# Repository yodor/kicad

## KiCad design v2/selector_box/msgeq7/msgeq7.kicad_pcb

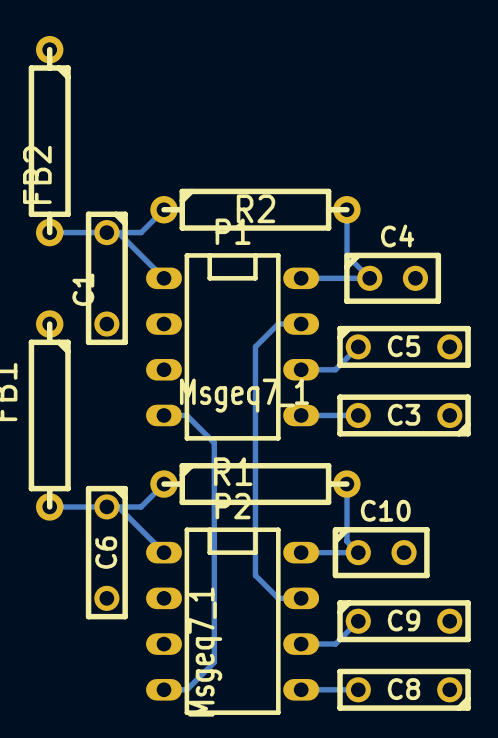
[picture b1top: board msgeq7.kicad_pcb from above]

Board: 2 copper layers, 14 parts (0 on the bottom side), 12 nets.

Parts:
C1, C5, C6, C9: 100nF; C2
C3, C8: 1uF; C2
C4, C10: 33pF; C1
FB1, FB2: FILTER; R4
P1, P2: Msgeq7_1; DIP-8__300
R1, R2: 200K; R4

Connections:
/5V: FB1.1, FB2.1
/RST: P1.7, P2.7
/Strobe: P1.4, P2.4
GND: C1.2, C4.2, C5.2, C6.2, C9.2, C10.2, P1.2, P2.2
unnamed: C9.1, P2.6
unnamed: C10.1, P2.8, R1.2
unnamed: C8.2, P2.5
unnamed: C6.1, FB1.2, P2.1, R1.1
unnamed: C5.1, P1.6
unnamed: C3.2, P1.5
unnamed: C1.1, FB2.2, P1.1, R2.1
unnamed: C4.1, P1.8, R2.2

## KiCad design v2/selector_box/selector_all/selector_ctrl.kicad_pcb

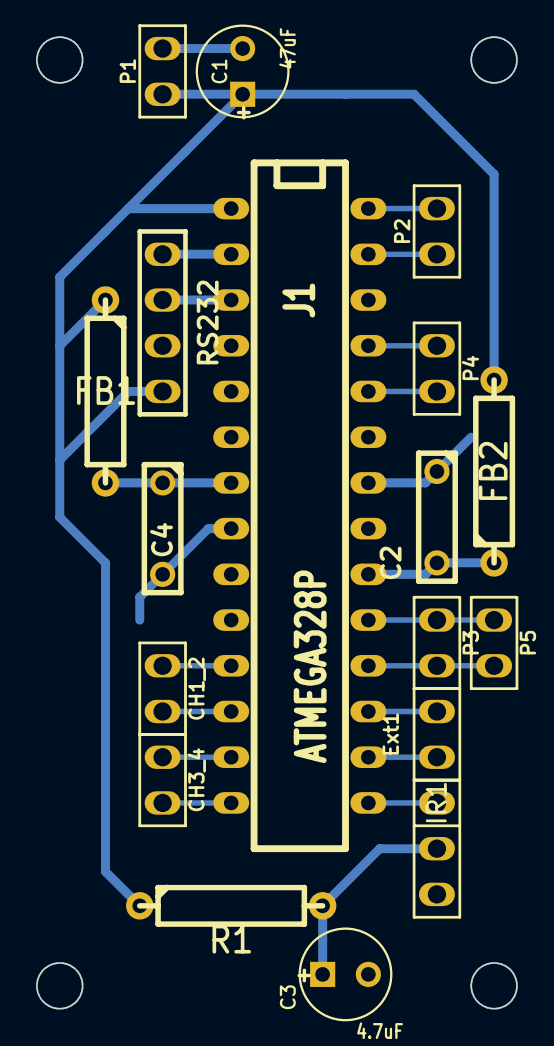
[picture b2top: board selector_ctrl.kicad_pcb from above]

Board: 2 copper layers, 26.7 x 54.0 mm, 18 parts (0 on the bottom side), 20 nets.

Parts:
C1: 47uF; C1V5
C2, C4: 100nF; C2
C3: 4.7uF; C1V5
CH1_2, CH3_4: CONN_2; PIN_ARRAY_2X1
Ext1: CONN_2; PIN_ARRAY_2X1
FB1, FB2: FILTER; R4
IR1: CONN_3; PIN_ARRAY_3X1
J1: ATMEGA328P; DIP-28__300
P1, P2, P3, P4, P5: CONN_2; PIN_ARRAY_2X1
R1: 100R; R4
RS232: CONN_4; PIN_ARRAY_4x1

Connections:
/5V: C1.1, FB1.1, FB2.2, J1.1, P1.1, R1.1, RS232.4
/CH1: CH1_2.1, J1.11
/CH2: CH1_2.2, J1.12
/CH3: CH3_4.1, J1.13
/CH4: CH3_4.2, J1.14
/EQ7_DATA_L: J1.25, P4.1
/EQ7_DATA_R: J1.24, P4.2
/EQ7_RST: J1.18, P3.2, P5.2
/EQ7_STROBE: J1.19, P3.1, P5.1
/EXT1: Ext1.1, J1.17
/EXT2: Ext1.2, J1.16
/IR: IR1.1, J1.15
/RX: J1.2, RS232.1
/SCL: J1.28, P2.2
/SDA: J1.27, P2.1
/TX: J1.3, RS232.2
GND: C1.2, C2.1, C3.2, C4.2, IR1.3, J1.8, J1.22, P1.2, RS232.3
unnamed: C2.2, FB2.1, J1.20
unnamed: C4.1, FB1.2, J1.7
unnamed: C3.1, IR1.2, R1.2

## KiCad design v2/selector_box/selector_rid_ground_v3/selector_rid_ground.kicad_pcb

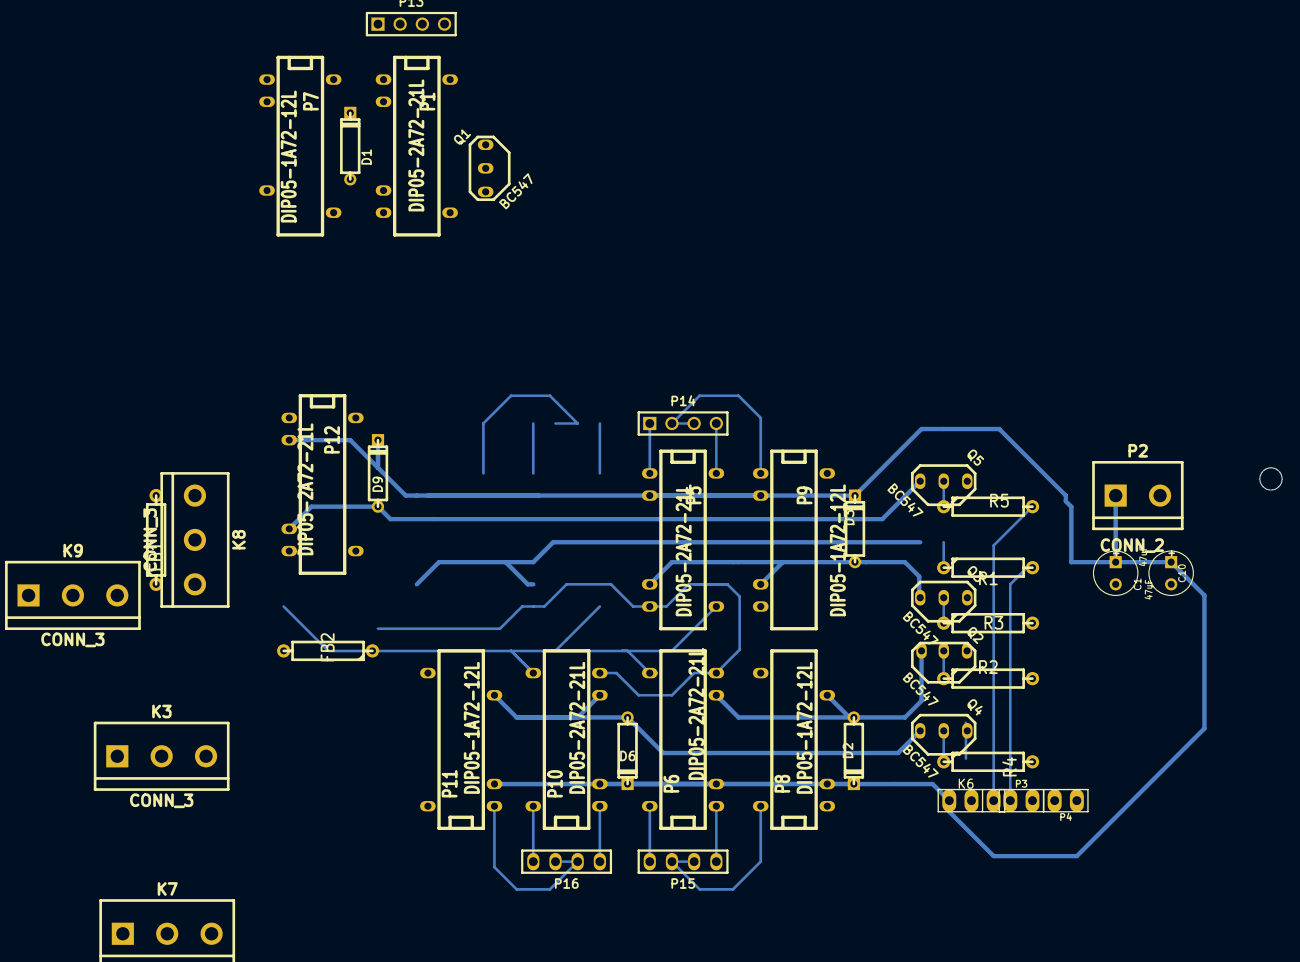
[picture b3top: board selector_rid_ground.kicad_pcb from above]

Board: 2 copper layers, 40 parts (0 on the bottom side), 34 nets.

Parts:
C1, C10: 47uF; C1V5
D1, D2, D3, D6, D9: DIODE; D3
FB1, FB2: FILTER; R4
K3, K7, K8, K9: CONN_3; bornier3
K6: CONN_3; PIN_ARRAY_3X1
P1, P5, P6, P10, P12: DIP05-2A72-21L; DIP-14__300
P2: CONN_2; bornier2
P3, P4: CONN_2; PIN_ARRAY_2X1
P7, P8, P9, P11: DIP05-1A72-12L; DIP-14__300
P13, P14, P15, P16: CONN_4; PIN_ARRAY_4x1
Q1, Q2, Q3, Q4, Q5: BC547; bc547
R1, R2, R3, R4, R5: 12K; R4

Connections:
/EN1: P3.1, R1.2
/EN2: P3.2, R3.2
/EN3: P4.1, R2.2
/EN4: P4.2, R4.2
/EN_MUTE: K6.1, R5.2
/G_IN1: P7.14, P13.2, P13.3
/G_IN2: P9.1, P14.2, P14.3
/G_IN3: P8.14, P15.2, P15.3
/G_IN4: P11.1, P16.2, P16.3
/G_OUT: K3.2, K7.2, K8.2, K9.2, P7.8, P8.8, P9.8, P11.8, P12.1, P12.14
/L_IN1: P1.1, P13.1
/L_IN2: P5.1, P14.1
/L_IN3: P6.1, P15.1
/L_IN4: P10.1, P16.1
/L_OUT: FB1.1, K3.3, K7.1, K9.3, P1.7, P5.7, P6.7, P10.7, P12.8
/R_IN1: P1.14, P13.4
/R_IN2: P5.14, P14.4
/R_IN3: P6.14, P15.4
/R_IN4: P10.14, P16.4
/R_OUT: FB2.1, K3.1, K7.3, K9.1, P1.8, P5.8, P6.8, P10.8, P12.7
/VCC: C1.1, C10.1, D1.2, D2.2, D3.2, D6.2, D9.2, K6.3, P1.2, P2.1, P5.2, P6.2, P7.2, P8.2, P9.2, P10.2, P11.2, P12.2
GND: C1.2, C10.2, K6.2, P2.2, Q1.3, Q2.3, Q3.3, Q4.3, Q5.3
unnamed: D6.1, P10.6, P11.6, Q4.1
unnamed: D9.1, P12.6, Q5.1
unnamed: Q5.2, R5.1
unnamed: Q2.2, R2.1
unnamed: Q4.2, R4.1
unnamed: D2.1, P6.6, P8.6, Q2.1
unnamed: FB1.2, K8.1
unnamed: FB2.2, K8.3
unnamed: D1.1, P1.6, P7.6, Q1.1
unnamed: Q1.2, R1.1
unnamed: Q3.2, R3.1
unnamed: D3.1, P5.6, P9.6, Q3.1

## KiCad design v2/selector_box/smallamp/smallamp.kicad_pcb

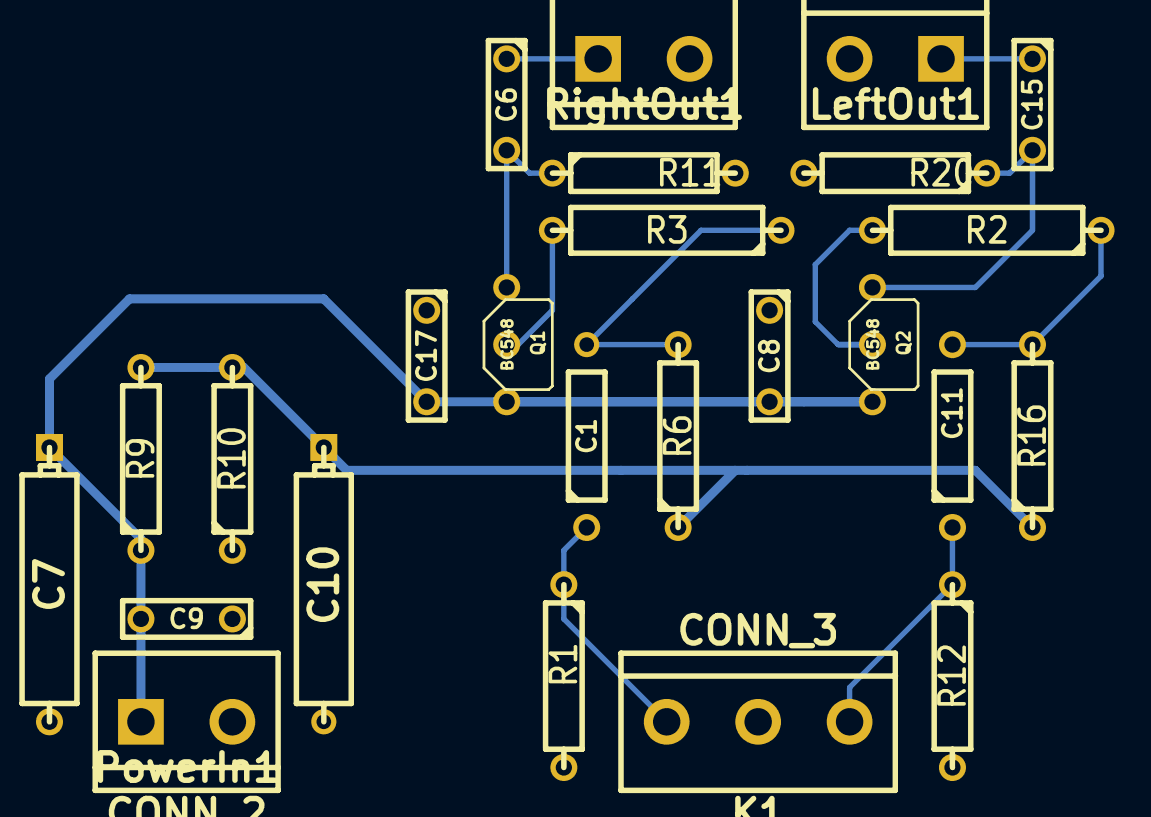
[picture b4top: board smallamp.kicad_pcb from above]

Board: 2 copper layers, 25 parts (0 on the bottom side), 13 nets.

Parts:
C1, C11: 0.047uF; C2
C6, C8, C9, C15, C17: 100nF; C2
C7, C10: 2.2uF TANT; CP6
K1: CONN_3; bornier3
LeftOut1: CONN_2; bornier2
PowerIn1: CONN_2; bornier2
Q1, Q2: BC548; TO92PN
R1, R12: 470K; R4
R2, R3: FB; R5
R6, R16: 47K; R4
R9, R10: 10K; R4
R11, R20: 2.2K; R4
RightOut1: CONN_2; bornier2

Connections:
2.5V: C10.1, R6.1, R9.2, R10.2, R16.1
5V: C7.1, C8.2, C9.2, C17.2, PowerIn1.1, Q1.1, Q2.1, R9.1
/CH1_L: C11.1, K1.1, R12.1
/CH1_R: C1.1, K1.3, R1.1
/LEFT_OUT: C15.1, LeftOut1.1
/RIGHT_OUT: C6.1, RightOut1.1
GND: C7.2, C8.1, C9.1, C10.2, C17.1, K1.2, LeftOut1.2, PowerIn1.2, R1.2, R10.1, R11.2, R12.2, R20.2, RightOut1.2
unnamed: C11.2, R2.1, R16.2
unnamed: Q2.2, R2.2
unnamed: Q1.2, R3.2
unnamed: C1.2, R3.1, R6.2
unnamed: C6.2, Q1.3, R11.1
unnamed: C15.2, Q2.3, R20.1

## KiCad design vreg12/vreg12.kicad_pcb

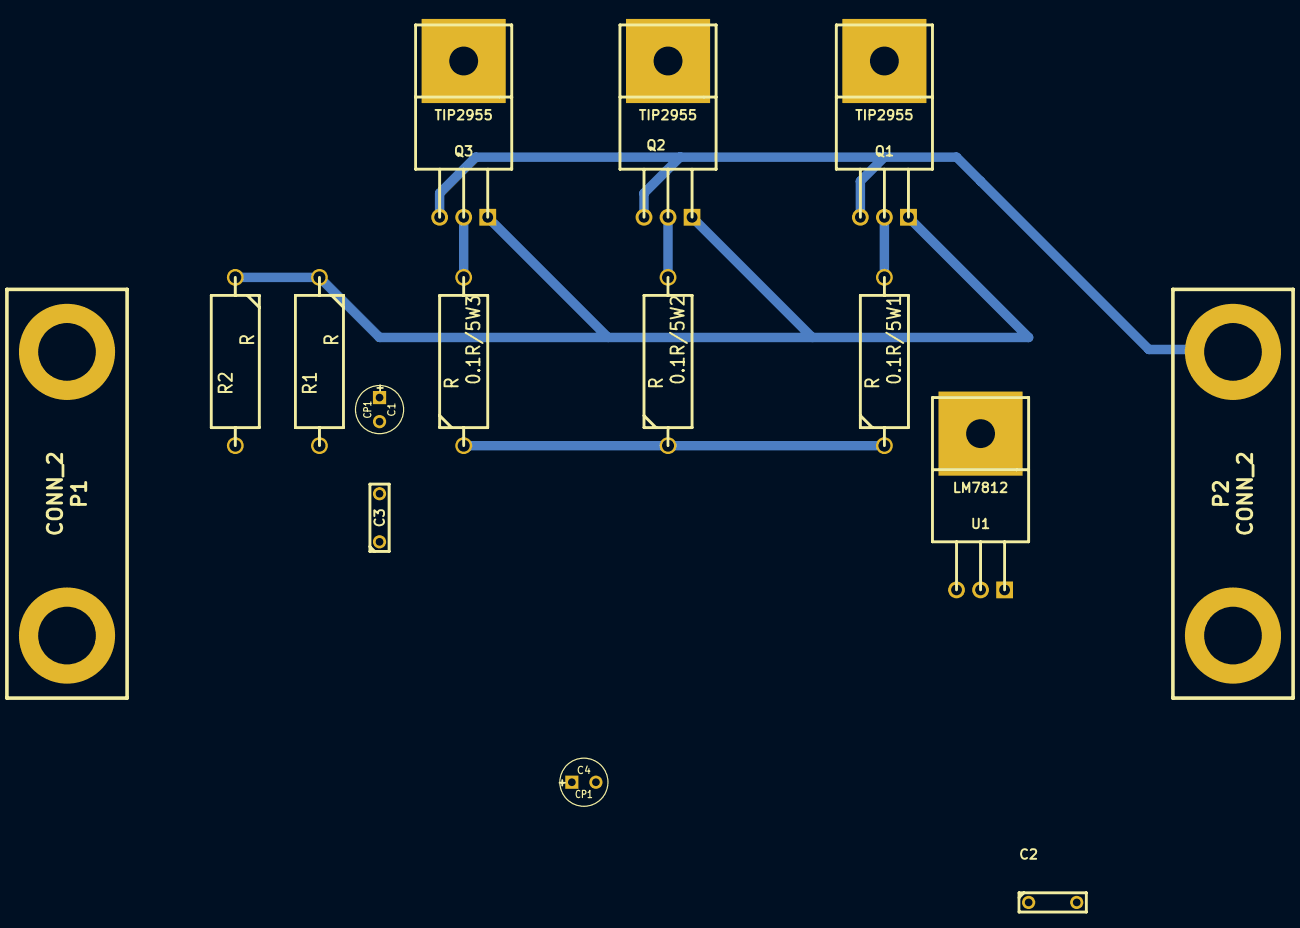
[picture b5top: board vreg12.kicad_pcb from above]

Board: 2 copper layers, 15 parts (0 on the bottom side), 7 nets.

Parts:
0.1R/5W1, 0.1R/5W2, 0.1R/5W3: R; R7
C1, C4: CP1; C1V5
C2, C3: C; C2
P1, P2: CONN_2; 2PIN_6mm
Q1, Q2, Q3: TIP2955; TO220
R1, R2: R; R7
U1: LM7812; TO220

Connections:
unnamed: C3.1, C4.1, P2.1, Q1.2, Q2.2, Q3.2
unnamed: C1.2, C2.2, C3.2, C4.2, P1.1, P2.2
unnamed: 0.1R/5W1.2, Q1.3
unnamed: 0.1R/5W2.2, Q2.3
unnamed: 0.1R/5W3.2, Q3.3
unnamed: C1.1, C2.1, Q1.1, Q2.1, Q3.1, R1.1, R2.1
unnamed: 0.1R/5W1.1, 0.1R/5W2.1, 0.1R/5W3.1, P1.2, R1.2, R2.2
